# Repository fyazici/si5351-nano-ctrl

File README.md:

si5351-nano-ctrl
==

This is a simple Arduino Nano project to control the commonly available SI5351 oscillator board (originally from Adafruit). 1.44" SPI TFT/OLED screen is used as the graphical interface. A rotary encoder and 4 buttons allow menu navigation and frequency adjustments.

Features include:
* Full range of frequencies from 2.5 kHz up to 300 MHz (with PLL overclock, performance guaranteed range limited to 225 MHz, see AN619).
* Automatic selection of PLL operation modes based on frequencies requested.
* Adjustable drive strength.
* Up to 6 presets can be saved to EEPROM. Loads `Preset 0` at startup.
* Xtal frequency correction, also stored on EEPROM.

Provided KiCad design is suitable for one-sided PCBs, e.g. made by toner transfer method at home. For two or more layers, PCB design can be optimized to reduce noise and unwanted coupling of SPI signals to the output.

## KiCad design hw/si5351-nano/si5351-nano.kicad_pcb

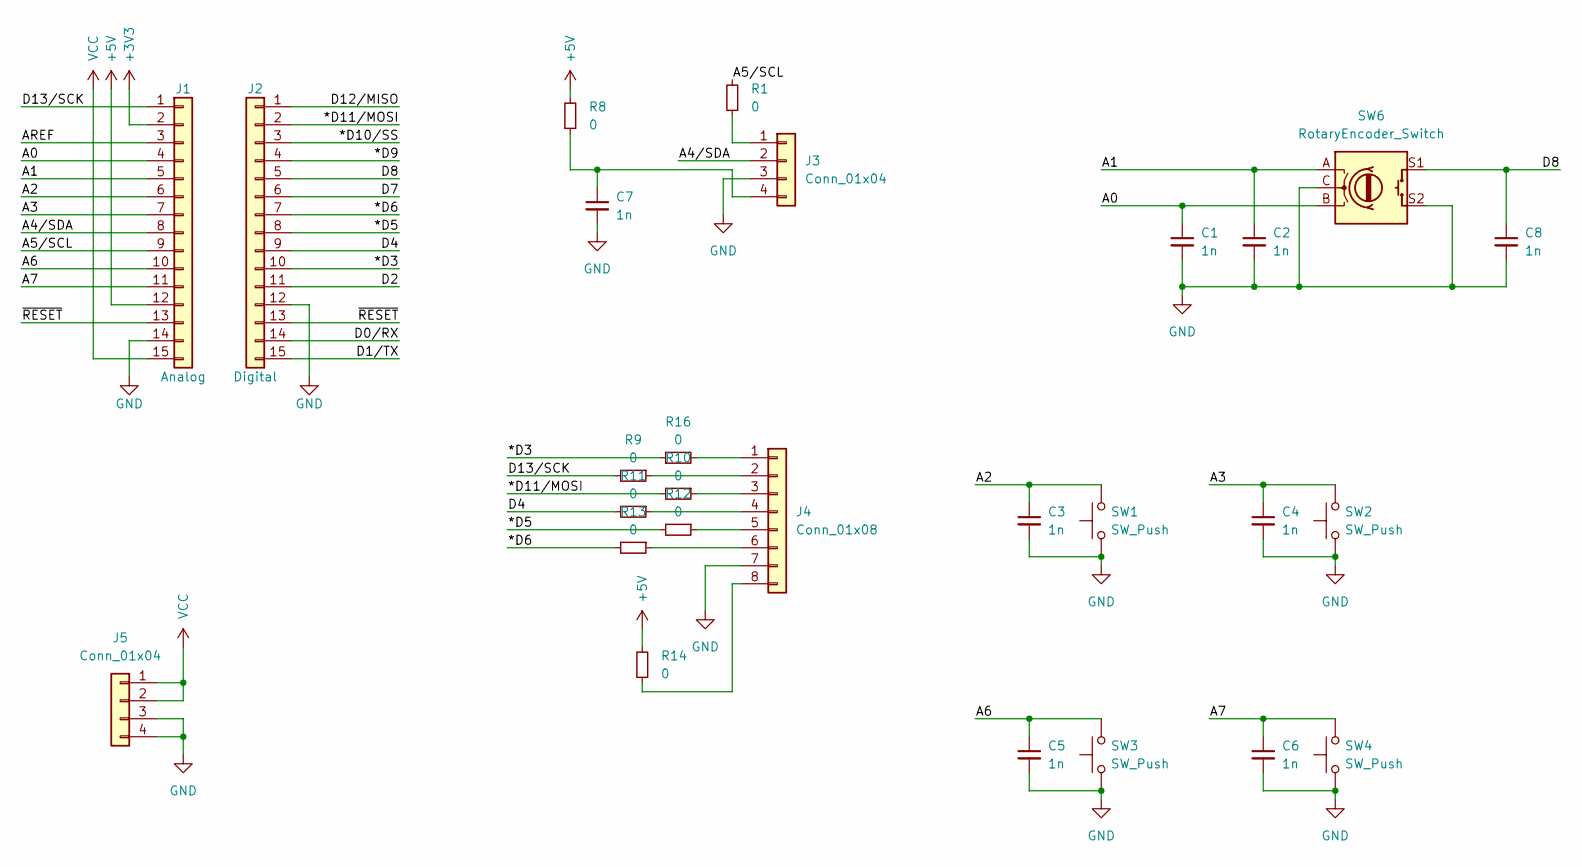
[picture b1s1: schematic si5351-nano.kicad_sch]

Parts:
C1, C2, C3, C4, C5, C6, C7, C8: 1n; C_1206_3216Metric
J1: Analog; PinHeader_1x15_P2.54mm_Vertical
J2: Digital; PinHeader_1x15_P2.54mm_Vertical
J3, J5: Conn_01x04; PinHeader_1x04_P2.54mm_Vertical
J4: Conn_01x08; PinHeader_1x08_P2.54mm_Vertical
R1, R8, R9, R10, R11, R12, R13, R14, R16: 0; R_1206_3216Metric
SW1, SW2, SW3, SW4: SW_Push; SW_PUSH_6mm
SW6: RotaryEncoder_Switch; RotaryEncoder_Alps_EC11E-Switch_Vertical_H20mm

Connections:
+3V3: J1.2
+5V: J1.12, R8.2, R14.2
/*D3: J2.10, R16.1
/*D5: J2.8, R12.2
/*D6: J2.7, R13.2
/*D9: J2.4
/*D10/SS: J2.3
/*D11/MOSI: J2.2, R10.2
/A0: C1.1, J1.4, SW6.B
/A1: C2.1, J1.5, SW6.A
/A2: C3.1, J1.6, SW1.2
/A3: C4.1, J1.7, SW2.2
/A4/SDA: J1.8, J3.2
/A5/SCL: J1.9, R1.2
/A6: C5.1, J1.10, SW3.2
/A7: C6.1, J1.11, SW4.2
/AREF: J1.3
/D0/RX: J2.14
/D1/TX: J2.15
/D2: J2.11
/D4: J2.9, R11.2
/D7: J2.6
/D8: C8.1, J2.5, SW6.S1
/D12/MISO: J2.1
/D13/SCK: J1.1, R9.2
/~RESET: J1.13, J2.13
GND: C1.2, C2.2, C3.2, C4.2, C5.2, C6.2, C7.2, C8.2, J1.14, J2.12, J3.3, J4.7, J5.3, J5.4, SW1.1, SW2.1, SW3.1, SW4.1, SW6.C, SW6.S2
unnamed: J3.1, R1.1
unnamed: C7.1, J3.4, R8.1
unnamed: J4.1, R16.2
unnamed: J4.2, R9.1
unnamed: J4.3, R10.1
unnamed: J4.4, R11.1
unnamed: J4.5, R12.1
unnamed: J4.6, R13.1
unnamed: J4.8, R14.1
VCC: J1.15, J5.1, J5.2

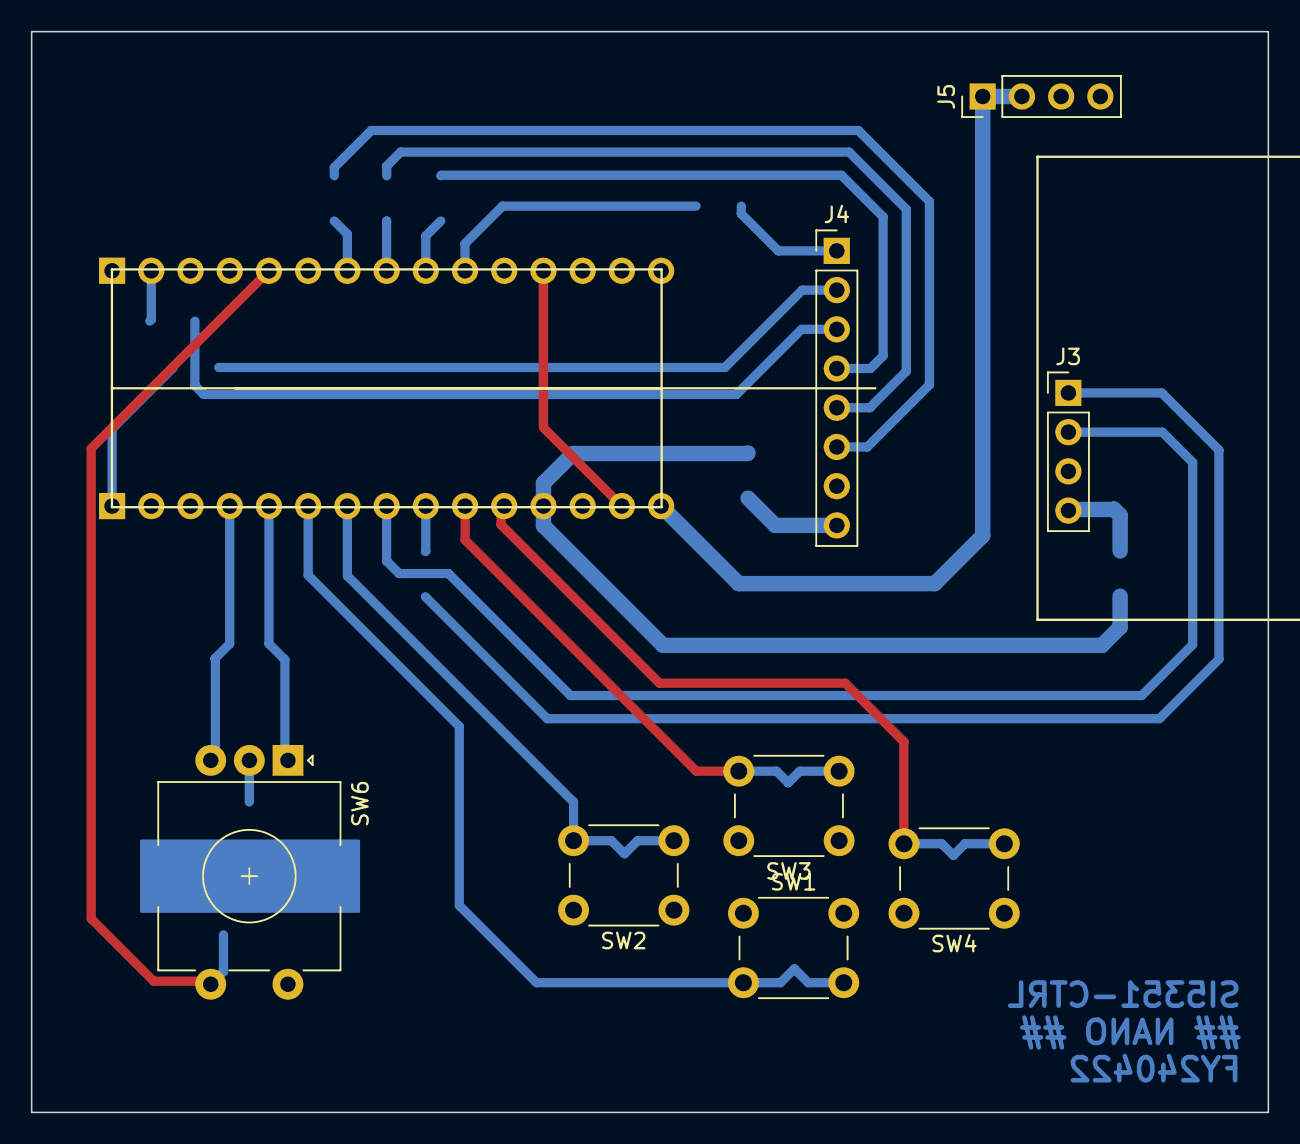
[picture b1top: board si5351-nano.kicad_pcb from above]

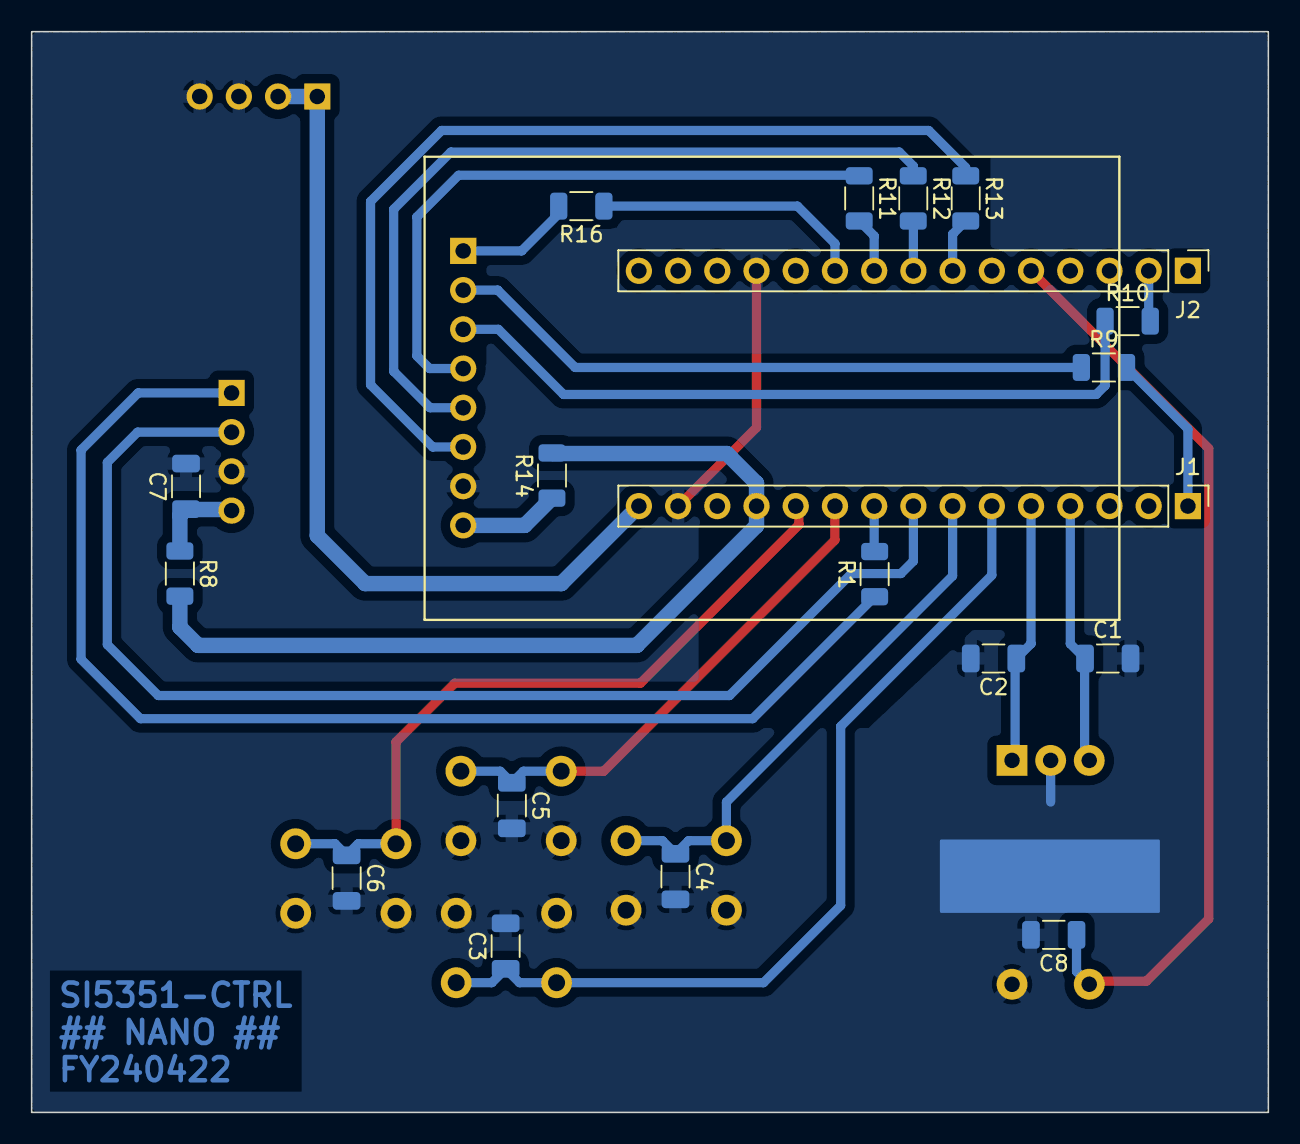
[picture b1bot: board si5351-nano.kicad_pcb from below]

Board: 2 copper layers, 80.1 x 70.0 mm, 27 parts (19 on the bottom side), 28 nets.

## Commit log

2024-05-25 fixed drive strength issue. added info screen.
2024-05-25 added release binaries.
2024-05-26 return from divby4 (>150M) bug fixed.
2024-05-26 set output powerdown when not enabled.
2024-06-28 added simple shell for reg access. display timeout. preset load bug fix. debug cleanup. removed build outputs.
